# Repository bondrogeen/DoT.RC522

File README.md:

# RC522

Physical Access Control System. ESP8266 MFRC522 RFID-Reader

The plugin for [DoT](https://github.com/bondrogeen/DoT)

or run manually

```lua

RC522={
  run=true,
  pin_ss = 0,
  time = 500,
  pin_relay =1,
  del_relay =1000,
  pin_buz = 2,
  pin_btn = 4  
}

pause=0
spi.setup(1, spi.MASTER, spi.CPOL_LOW, spi.CPHA_LOW, spi.DATABITS_8, 0)
print(dofile("RC522_SPI.lua")({init=true,pin=RC522.pin_ss}))
print(dofile("RC522_dev.lua")({init=true}))
  
RC522.timer = tmr.create()
RC522.timer:register(1000, tmr.ALARM_AUTO, function()
 local isTagNear, cardType = dofile("RC522_SPI.lua")({request=true,pin=RC522.pin_ss})
 if pause~=0 then pause=pause-1 end
 if isTagNear and pause==0 then
  RC522.timer:stop()
  local serialNo = dofile("RC522_SPI.lua")({anticoll=true,pin=RC522.pin_ss})   
  print(serialNo)
  if serialNo then 
   if RC522.mode=="add"then 
    print(dofile("RC522_key.lua")({add=serialNo})) 
    dofile("RC522_dev.lua")({buz=300})
   end
   if not RC522.mode or RC522.mode=="auth"then 
    pause=10
    local access = dofile("RC522_key.lua")({auth=serialNo})
    print(type (access)) 
    dofile("RC522_dev.lua")({relay=access})
   end
   if RC522.mode=="del"then 
    print(dofile("RC522_key.lua")({del=serialNo})) 
    dofile("RC522_dev.lua")({buz=300})
   end
  end
  RC522.timer:start()
 end
end)
RC522.timer:interval(500)
RC522.timer:start()

```

## Pin connection

## Screenshot DoT

## Changelog

### 0.0.3 (2018-05-02)
* (bondrogeen) Test version.
### 0.0.1 (2018-04-04)
* (bondrogeen) init.

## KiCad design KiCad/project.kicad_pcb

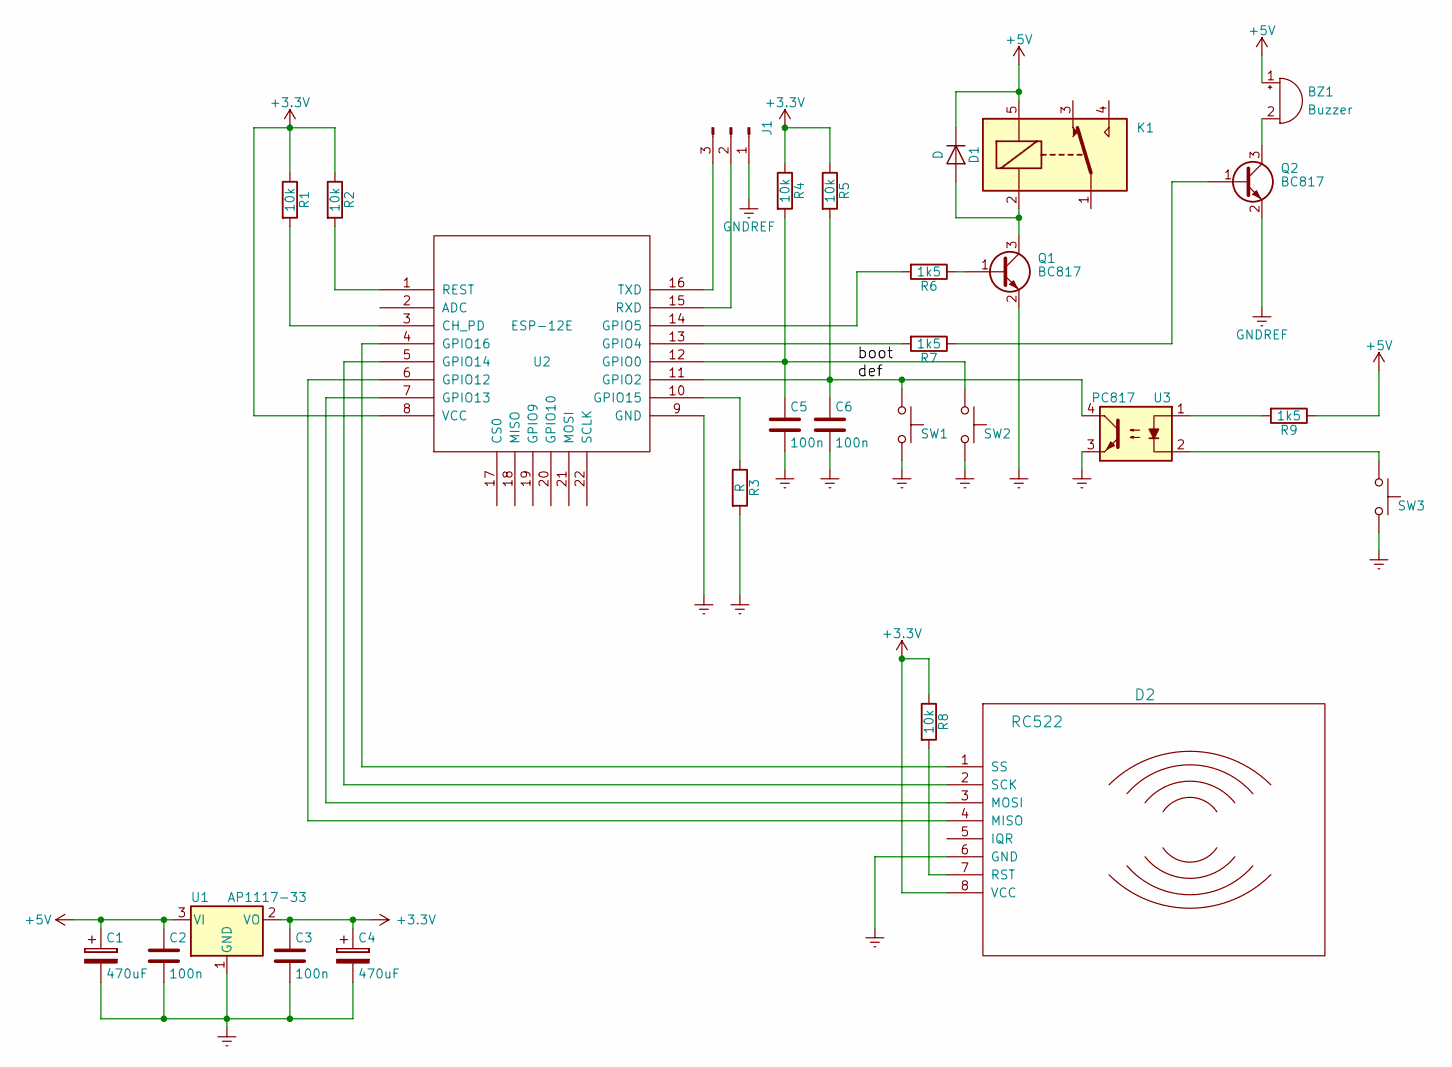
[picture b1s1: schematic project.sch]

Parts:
BZ1: Buzzer; BUZZER
C1, C4: 470uF; CP_Radial_D8.0mm_P3.80mm
C2, C3, C5, C6: 100n; C_0805
D1: D; D_2010
D2: RC522; Pin_Header_Straight_1x08_Pitch2.54mm
J1: Conn_01x03_Male; Pin_Header_Straight_1x04_Pitch2.54mm
K1: SANYOU_SRD_Form_C; Relay_SPDT_SANYOU_SRD_Series_Form_C
Q1, Q2: BC817; SOT-23
R1, R2, R4, R5, R8: 10k; R_0805
R3: R; R_0805
R6, R7, R9: 1k5; R_0805
SW1, SW2, SW3: SW_Push; SW_SPST_SKQG
U1: AP1117-33; SOT-223-3_TabPin2
U2: ESP-12E
U3: PC817; DIP-4_W7.62mm

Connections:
+3V3: C3.1, C4.1, D2.8 (VCC), R1.1, R2.1, R4.1, R5.1, R8.1, U1.2 (VO), U2.8 (VCC)
+5V: BZ1.1 (-), C1.1, C2.1, D1.1 (K), K1.5, R9.1, U1.3 (VI)
/boot: C5.1, R4.2, SW2.1, U2.12 (GPIO0)
/def: C6.1, R5.2, SW1.1, U2.11 (GPIO2), U3.4
GNDREF: C1.2, C2.2, C3.2, C4.2, C5.2, C6.2, D2.6 (GND), J1.1, Q1.2 (E), Q2.2 (E), R3.2, SW1.2, SW2.2, SW3.2, U1.1 (GND), U2.9 (GND), U3.3
unnamed: BZ1.2 (+), Q2.3 (C)
unnamed: D1.2 (A), K1.2, Q1.3 (C)
unnamed: D2.1 (SS), U2.4 (GPIO16)
unnamed: D2.2 (SCK), U2.5 (GPIO14)
unnamed: D2.3 (MOSI), U2.7 (GPIO13)
unnamed: D2.4 (MISO), U2.6 (GPIO12)
unnamed: D2.7 (RST), R8.2
unnamed: J1.2, U2.15 (RXD)
unnamed: J1.3, U2.16 (TXD)
unnamed: Q1.1 (B), R6.1
unnamed: Q2.1 (B), R7.1
unnamed: R1.2, U2.3 (CH_PD)
unnamed: R2.2, U2.1 (REST)
unnamed: R3.1, U2.10 (GPIO15)
unnamed: R6.2, U2.14 (GPIO5)
unnamed: R7.2, U2.13 (GPIO4)
unnamed: R9.2, U3.1
unnamed: SW3.1, U3.2

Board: 2 copper layers, 28 parts (0 on the bottom side), 23 nets, no tracks yet.

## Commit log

2018-04-04 init
2018-05-02 test
2018-12-17 minor fix
